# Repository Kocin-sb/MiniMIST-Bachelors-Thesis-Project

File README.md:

# MiniMIST-Bachelors-Thesis-Project
The MiniMIST is a model Satellite used for teaching STEM concepts. The thesis project is used at KTH Royal Institute of Technology for teaching purposes. The project involved making hardware design, programming the microcontroller, and developing a web page.

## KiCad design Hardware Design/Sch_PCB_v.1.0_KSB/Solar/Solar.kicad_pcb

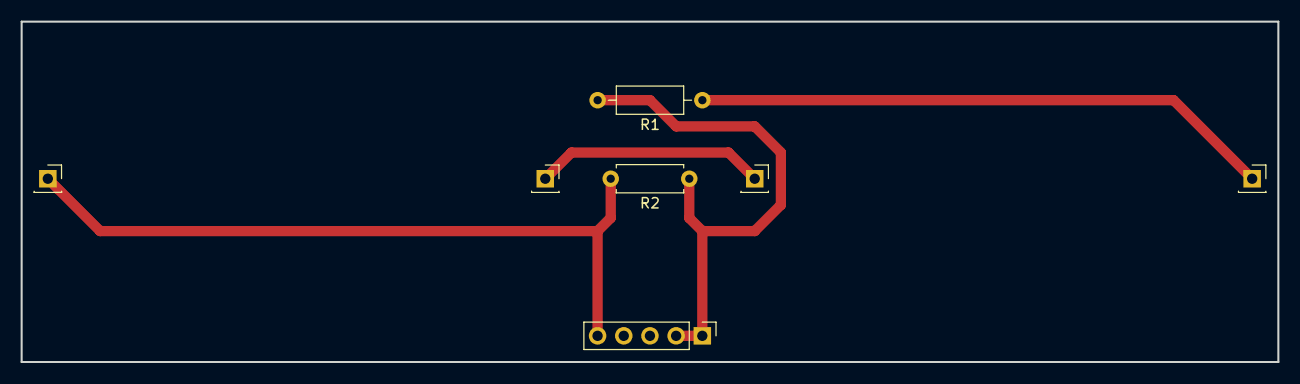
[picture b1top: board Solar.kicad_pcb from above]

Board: 2 copper layers, 121.9 x 33.0 mm, 7 parts (0 on the bottom side), 4 nets.

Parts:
R1: 22000; R_Axial_DIN0207_L6.3mm_D2.5mm_P10.16mm_Horizontal
R2: 8000; R_Axial_DIN0207_L6.3mm_D2.5mm_P7.62mm_Horizontal
Solar1conn1, Solar2conn1: Conn_01x01_Male; PinSocket_1x01_P2.54mm_Vertical
SolarJoin1, SolarJoin2: Conn_01x01_Male; PinSocket_1x01_P2.54mm_Vertical
SolarPanelConnector1: Conn_01x05_Male; PinHeader_1x05_P2.54mm_Vertical

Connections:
/Solar1Pos: R1.1, Solar1conn1.1
/Solar2Neg: R2.2, Solar2conn1.1, SolarPanelConnector1.5
unnamed: R1.2, R2.1, SolarPanelConnector1.1, SolarPanelConnector1.2
unnamed: SolarJoin1.1, SolarJoin2.1

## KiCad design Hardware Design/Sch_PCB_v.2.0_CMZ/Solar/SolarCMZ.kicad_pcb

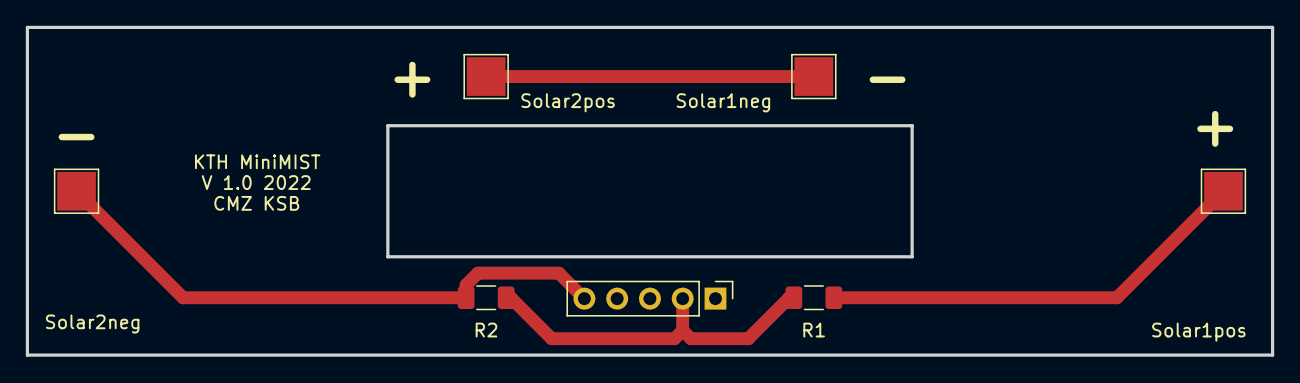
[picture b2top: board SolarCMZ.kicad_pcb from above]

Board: 2 copper layers, 96.5 x 25.4 mm, 7 parts (0 on the bottom side), 4 nets.

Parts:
R1: 22000; R_1206_3216Metric_Pad1.30x1.75mm_HandSolder
R2: 8000; R_1206_3216Metric_Pad1.30x1.75mm_HandSolder
Solar1neg, Solar1pos, Solar2neg, Solar2pos: Conn_01x01_Male; TestPoint_Pad_3.0x3.0mm
SolarPanelConnector1: Conn_01x05_Male; PinHeader_1x05_P2.54mm_Vertical

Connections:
/Solar1Pos: R1.1, Solar1pos.1
/Solar2Neg: R2.2, Solar2neg.1, SolarPanelConnector1.5
unnamed: R1.2, R2.1, SolarPanelConnector1.2
unnamed: Solar1neg.1, Solar2pos.1

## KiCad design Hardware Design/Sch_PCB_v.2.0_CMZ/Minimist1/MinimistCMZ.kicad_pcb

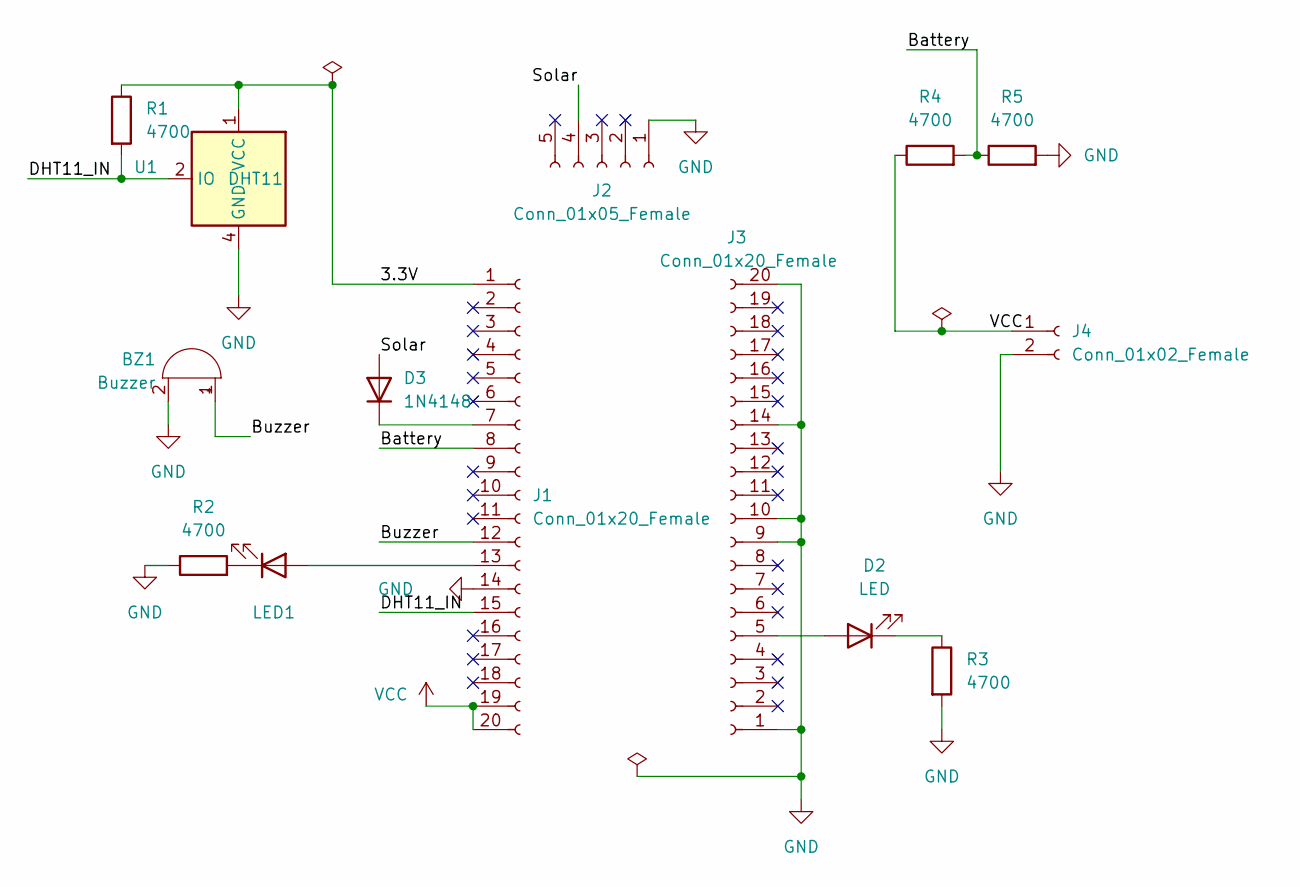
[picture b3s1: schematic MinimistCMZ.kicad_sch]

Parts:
BZ1: Buzzer; Buzzer_12x9.5RM7.6
D2: LED
D3: 1N4148
J1, J3: Conn_01x20_Female; PinSocket_1x20_P2.54mm_Vertical
J2: Conn_01x05_Female; PinSocket_1x05_P2.54mm_Vertical
J4: Conn_01x02_Female; PinSocket_1x02_P2.54mm_Vertical
LED1: (no value)
R1, R2, R3, R4, R5: 4700
U1: DHT11; Aosong_DHT11_5.5x12.0_P2.54mm

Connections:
/3.3V: J1.1, R1.1, U1.1 (VCC)
/Battery: J1.8, R4.2, R5.1
/Buzzer: BZ1.1 (-), J1.12
/DHT11_IN: J1.15, R1.2, U1.2 (IO)
/Solar: D3.2 (A), J2.4
GND: BZ1.2 (+), J1.14, J2.1, J3.1, J3.9, J3.10, J3.14, J3.20, J4.2, R2.1, R3.2, R5.2, U1.4 (GND)
unnamed: D2.1 (K), R3.1
unnamed: D2.2 (A), J3.5
unnamed: D3.1 (K), J1.7
unnamed: J1.13, LED1.2 (A)
unnamed: LED1.1 (K), R2.2
VCC: J1.19, J1.20, J4.1, R4.1

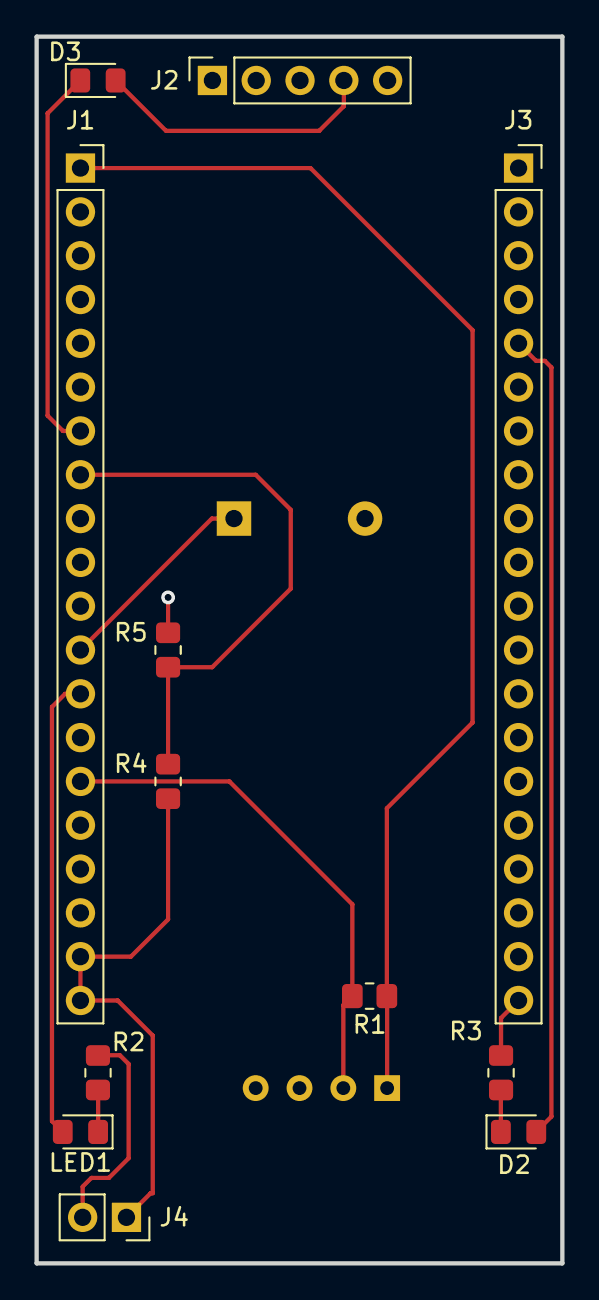
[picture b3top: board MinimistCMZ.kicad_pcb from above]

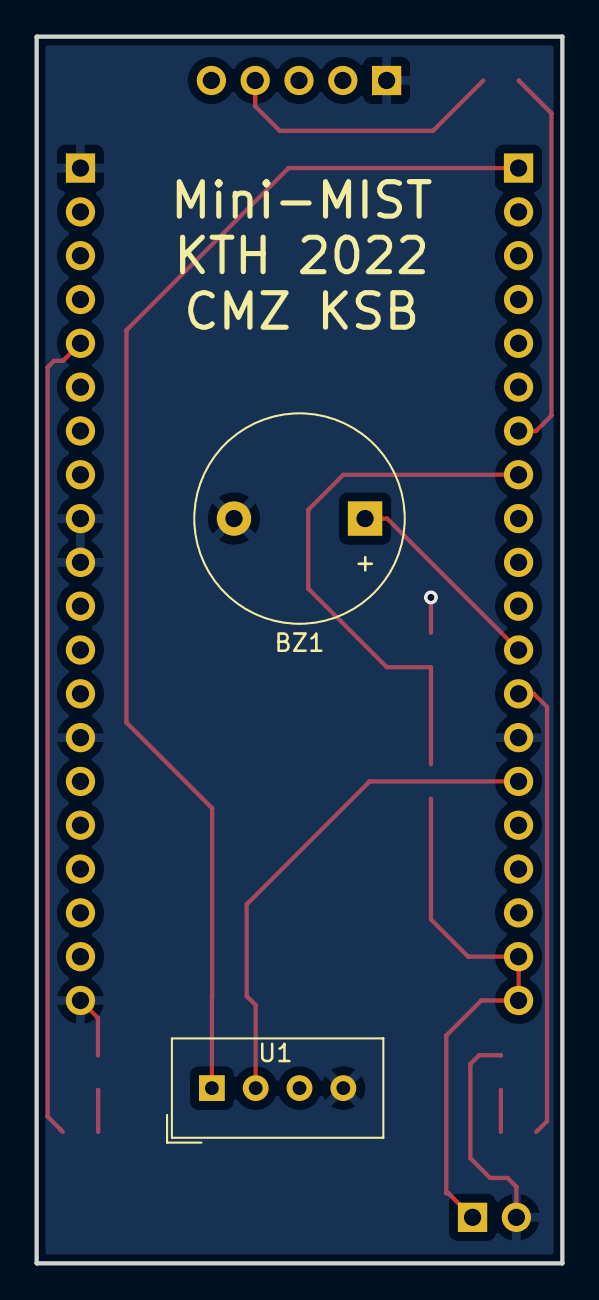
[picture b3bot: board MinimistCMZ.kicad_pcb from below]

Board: 2 copper layers, 30.5 x 71.1 mm, 14 parts (2 on the bottom side), 12 nets.

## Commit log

2022-09-12 Hardware Design Added
